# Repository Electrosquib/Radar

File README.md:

# Radar

How to use:
1) git clone https://github.com/Electrosquib/Radar.git
2) cd Radar
3) python -m venv .venv (in WSL or a linux terminal)
4) source .venv/bin/activate
5) pip install -r requirements.txt
6) python Web\ App/api.py
7) Access it at http://127.0.0.1:5000/ on a web browser

Vivado project path: Processing\Vivado\AD936X_PL\projects\fmcomms2\zc702\zc702.xpr
Hardware Github: https://github.com/OpenSourceSDRLab/PlutoSky_7020_AD936X_SDR

Experimental synthetic-aperture radar (SAR) acquisition and processing code. The repository contains an interactive stepped-frequency continuous-wave (SFCW) workflow, reusable backprojection and autofocus algorithms, an FMCW/GNSS processing pipeline, example data, and KiCad hardware files.

Note: On windows you'll need to install the PlutoSDR drivers.

## Main files

- `Processing/Acquisition/SFCW/SAR.py` — interactive SFCW acquisition, rail control, scan persistence, and image generation
- `Processing/Acquisition/SFCW/SFCW.py` — AD936x/Pluto SDR configuration and SFCW range-profile acquisition
- `Processing/Imaging.py` — SAR backprojection
- `Processing/Autofocus.py` — minimum-entropy autofocus (MEA) and phase-gradient autofocus (PGA)
- `Processing/Acquisition/ProcessingFMCW/process_fmcw.py` — recorded FMCW and RTK/GNSS processing CLI
- `Processing/Examples/` — small algorithm experiments and examples

`Processing/Acquisition/SFCW/SAR.py` is the easiest entry point for the complete SFCW workflow. It combines the lower-level, hand-written processing functions into one interactive program.

## Requirements

- Python 3.10 or newer
- NumPy, SciPy, Matplotlib, Pillow, and Numba
- `pyadi-iio` for the SDR
- `pyserial` for the motion rail
- An AD936x-compatible SDR reachable through libiio (the default URI is `usb:`)
- A serial-controlled rail for new acquisitions
- Optional: FFmpeg/FFplay for scene-camera capture on macOS

Create and activate a virtual environment, then install the Python packages:

```sh
python -m venv .venv
```

On macOS/Linux:

```sh
source .venv/bin/activate
python -m pip install numpy scipy matplotlib pillow numba pyadi-iio pyserial soundfile
```

On Windows PowerShell:

```powershell
.venv\Scripts\Activate.ps1
python -m pip install numpy scipy matplotlib pillow numba pyadi-iio pyserial soundfile
```

The SDR also requires the platform-specific libiio drivers and USB permissions supplied by Analog Devices. Verify that the SDR is visible to libiio before starting an acquisition.

## Start the streaming range-profile viewer

From the repository root on Windows:

```powershell
.\.venv\Scripts\python.exe start_radar.py --rebuild
.\.venv\Scripts\python.exe start_radar.py
```

Use `--rebuild` once to compile and upload `Processing/Firmware/Apps/radar.c` over the USB serial console. Later launches reuse the installed PS binary. The launcher automatically finds the Pluto console (currently COM3), logs in, starts PS acquisition, receives its sweeps over USB, and opens the existing range-profile viewer in your browser. Uploads are checked with SHA-256 before replacing the PS binary.

The streaming firmware uses TX1/RX1 for the antennas and a TX2 → RX2 cable for the reference. TX2 attenuation is 10 dB; reference RX gain is 25 dB and antenna RX gain is 30 dB. The viewer prints completed sweeps per second (Hz), and its amplitude slider holds the trace and waterfall scales fixed.

Close any other program using the Pluto serial console before launching. Press Ctrl+C in the launcher terminal to stop capture and the viewer; closing only the browser tab does not stop capture. USB Ethernet, SSH, and an IP address are not required. The existing `.venv`, ARM compiler, Makefile, and pyserial package are used.

## Run the SFCW SAR workflow

First edit the configuration constants near the top of `Processing/Acquisition/SFCW/SAR.py` to match the equipment and desired image:

- `RAIL_PORT`, `RAIL_BAUD`, and the rail movement settings
- `DEVICE_STRING` (for example, `usb:` or an SDR network URI)
- `FMIN`, `FMAX`, and `FS`
- `RAIL_STEPS_TO_CAPTURE` and `RAIL_STEP_INCHES`
- `H_RADAR_FT`, `CROSSRANGE_FT`, `DOWNRANGE_FT`, and `IMAGING_RESOLUTION`

The checked-in `RAIL_PORT` is a macOS device path and will normally need to be changed on Linux or Windows.

From the repository root, run:

```sh
python Processing/Acquisition/SFCW/SAR.py
```

Enter a scene name when prompted. For a new scene:

- `s` starts a scan.
- `b` toggles background calibration for the run.
- `n` lets you choose a different scene name.

For an existing scene:

- `c` continues an interrupted acquisition.
- `g` regenerates all reports from the saved range profiles without connecting to the rail or SDR.
- `r` regenerates reports using a selected slant-range gate.
- `a` corrects the saved rail-position spacing.
- `b` toggles calibration before continuing or generating reports.

Before starting, make sure the rail can move safely through its entire configured travel. Press `Ctrl+C` to interrupt. Completed scans are saved after every rail position, so the same scene can be continued later. When resuming, position the rail at the next unsaved location exactly as the prompt describes.

### Output

Each scene is stored under `Processing/SAR Data/SFCW/<Scene Name>/`. A completed run can contain:

- `range_profiles.npz` — complex profiles, frequency information, and rail positions
- `metadata.json` — scan timestamps, positions, and run status
- `scene.png` — camera image or placeholder
- `bp.png` — backprojected image
- `mea.png` — minimum-entropy autofocus result
- `pga.png` — phase-gradient autofocus result
- `<scene_name>.png` — combined report image

Calibration is stored at `Processing/SAR Data/SFCW/Calibrate/calibration.npy`. Capture it against an empty/background scene using the calibration option, and only apply it to acquisitions made with compatible radar settings.

## Regenerate images from an existing SFCW scan

Run the same interactive program:

```sh
python Processing/Acquisition/SFCW/SAR.py
```

Enter the exact existing scene name and select `g`, or select `r` to restrict processing to a slant-range interval. This path only needs the scene's `range_profiles.npz`; it does not open the rail or SDR.

To change image bounds, resolution, dynamic range, or autofocus iteration counts, edit the corresponding constants near the top of `SAR.py` and regenerate the report.

## Use the processing functions in Python

Run scripts from the repository root and add `Processing` to the import path:

```python
import sys
from pathlib import Path

sys.path.insert(0, str(Path("Processing").resolve()))

import Autofocus
import Imaging

image, crossrange_axis, downrange_axis, complex_image = Imaging.backproject(
    positions=positions,             # antenna positions, in metres
    range_profiles=range_profiles,   # one complex profile per position
    crossrange=(-3.0, 3.0),          # metres
    downrange=(0.0, 6.0),            # metres
    resolution=(200, 200),
    fstart=start_frequency_hz,
    fstop=stop_frequency_hz,
    dr=range_bin_spacing_m,
    output_db=True,
    normalize_db=True,
)
```

See the full `Imaging.backproject()` signature and docstring for coordinate offsets, oversampling, phase sign, calibration, and output orientation. `Autofocus.py` exposes `minimum_entropy_autofocus()`, `parameterized_mea()`, and `phase_gradient_autofocus()` for correcting position or phase errors.

## Process recorded FMCW data with GNSS positions

The FMCW pipeline has its own detailed guide at `Processing/Acquisition/ProcessingFMCW/README.md`. Install its Python dependencies with:

```sh
python -m pip install -r Processing/Acquisition/ProcessingFMCW/requirements.txt
```

RTK position solving additionally requires the RTKLIB programs `convbin` and `rnx2rtkp` on `PATH`. Useful commands from the repository root are:

```sh
python Processing/Acquisition/ProcessingFMCW/process_fmcw.py inventory

python Processing/Acquisition/ProcessingFMCW/process_fmcw.py solve-rtcm \
  --rover-rtcm path/to/rover.rtcm3 \
  --base-rtcm path/to/base.rtcm3 \
  --output Processing/Acquisition/ProcessingFMCW/timestamped_locations.csv

python Processing/Acquisition/ProcessingFMCW/process_fmcw.py process-scans \
  --locations Processing/Acquisition/ProcessingFMCW/timestamped_locations.csv
```

Use `python Processing/Acquisition/ProcessingFMCW/process_fmcw.py --help` and the subcommand-specific `--help` output for input directories, channel selection, radar parameters, and image settings.

## AI use disclosure

Although the important code was human-generated for learning purposes, much of the non-critical boilerplate and tooling was made with ChatGPT. The core algorithms—including MEA, PGA, backprojection, and SFCW processing—are considered important and were hand-coded. Visualization, documentation, rail-control and integration code, and some ports of the MATLAB FMCW radar were created with AI assistance.

This is a long-standing project, so every AI-assisted file may not be identified. The general rule followed in this repository is: code with educational value is written manually; convenience and integration work may use AI assistance. For example, this README.md file was proofread and expounded on with AI.

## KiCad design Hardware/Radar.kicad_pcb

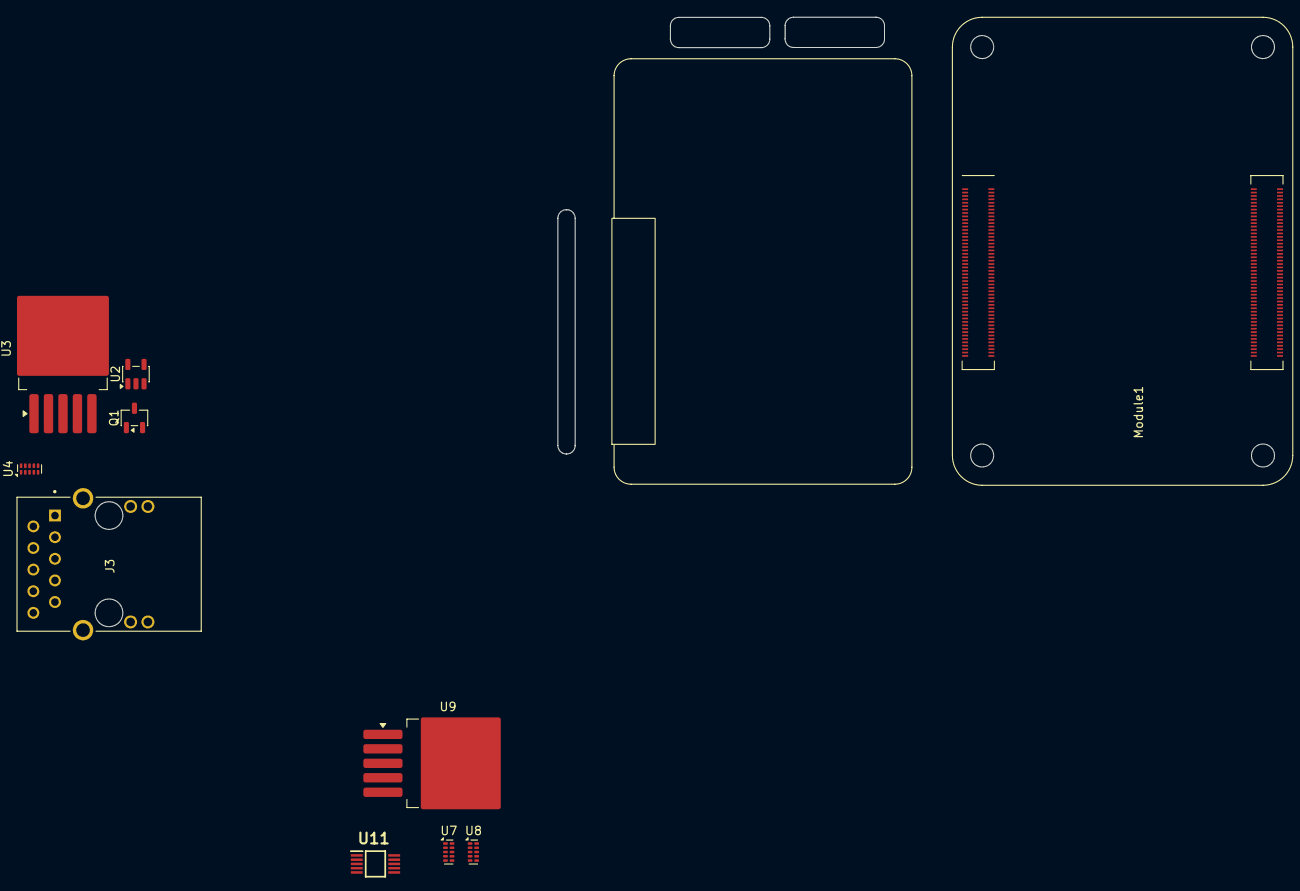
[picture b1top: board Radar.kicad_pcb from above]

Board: 2 copper layers, 10 parts (0 on the bottom side), 17 nets, no tracks yet.

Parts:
J3: RJMG201K21120FR; AMPHENOL_RJMG201K21120FR
Module1: ComputeModule4-CM4; CM4
Q1: DMP3013SFV; SOT-23-3
U2: TPS2069CDBV; SOT-23-5
U3: LM2576HVS-5; TO-263-5_TabPin3
U4, U7, U8: TPD4EUSB30; USON-10_2.5x1.0mm_P0.5mm
U9: LM2576HVS-3.3; TO-263-5_TabPin3
U11: MAX41461; SOP50P490X110-10N

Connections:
+1V8: Module1.88 (+1.8v_(Output)), Module1.90 (+1.8v_(Output))
+3V3: Module1.78 (GPIO_VREF(1.8v/3.3v_Input)), Module1.84 (+3.3v_(Output)), Module1.86 (+3.3v_(Output))
+5V: Module1.77 (+5v_(Input)), Module1.79 (+5v_(Input)), Module1.81 (+5v_(Input)), Module1.83 (+5v_(Input)), Module1.85 (+5v_(Input)), Module1.87 (+5v_(Input)), U2.5 (IN), U3.4 (FB)
+12V: Q1.1 (S), Q1.2 (S), Q1.3 (S), U3.1 (VIN), U9.1 (VIN)
/Compute/E0+: J3.P2 (TD1+), Module1.10 (Ethernet_Pair0_N), U7.1 (D1+)
/Compute/E0-: J3.P3 (TD1-), Module1.12 (Ethernet_Pair0_P), U7.2 (D1-)
/Compute/E1+: J3.P4 (TD2+), Module1.4 (Ethernet_Pair1_P), U7.4 (D2+)
/Compute/E1-: J3.P5 (TD2-), Module1.6 (Ethernet_Pair1_N), U7.5 (D2-)
/Compute/E2+: J3.P7 (TD3+), Module1.9 (Ethernet_Pair2_N), U8.1 (D1+)
/Compute/E2-: J3.P8 (TD3-), Module1.11 (Ethernet_Pair2_P), U8.2 (D1-)
/Compute/E3+: J3.P9 (TD4+), Module1.3 (Ethernet_Pair3_P), U8.4 (D2+)
/Compute/E3-: J3.P10 (TD4-), Module1.5 (Ethernet_Pair3_N), U8.5 (D2-)
/Compute/E_LED_G: J3.L4, Module1.17 (Ethernet_nLED2(3.3v))
/Compute/E_LED_Y: J3.L2, Module1.15 (Ethernet_nLED3(3.3v))
GND: J3.P1 (GND), J3.S1 (SHIELD), J3.S2 (SHIELD__1), Module1.101 (USB_OTG_ID), Module1.107 (GND), Module1.108 (GND), Module1.113 (GND), Module1.114 (GND), Module1.119 (GND), Module1.120 (GND), Module1.125 (GND), Module1.126 (GND), Module1.131 (GND), Module1.132 (GND), Module1.137 (GND), Module1.138 (GND), Module1.144 (GND), Module1.150 (GND), Module1.155 (GND), Module1.156 (GND), Module1.161 (GND), Module1.162 (GND), Module1.167 (GND), Module1.168 (GND), Module1.173 (GND), Module1.174 (GND), Module1.179 (GND), Module1.180 (GND), Module1.185 (GND), Module1.186 (GND), Module1.191 (GND), Module1.192 (GND), Module1.197 (GND), Module1.198 (GND), U2.2 (GND), U4.3 (GND), U4.8 (GND), U7.3 (GND), U7.8 (GND), U8.3 (GND), U8.8 (GND)
unnamed: Module1.1 (GND), Module1.7 (GND), Module1.13 (GND), Module1.23 (GND), Module1.33 (GND), Module1.43 (GND), Module1.53 (GND), Module1.59 (GND), Module1.65 (GND), Module1.71 (GND)
unnamed: Module1.2 (GND), Module1.8 (GND), Module1.14 (GND), Module1.22 (GND), Module1.32 (GND), Module1.42 (GND), Module1.52 (GND), Module1.60 (GND), Module1.66 (GND), Module1.74 (GND), Module1.98 (GND)
